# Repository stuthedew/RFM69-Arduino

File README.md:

RFM69-Arduino
=============

Arduino Library for the HopeRF RFM69HW Radio Module

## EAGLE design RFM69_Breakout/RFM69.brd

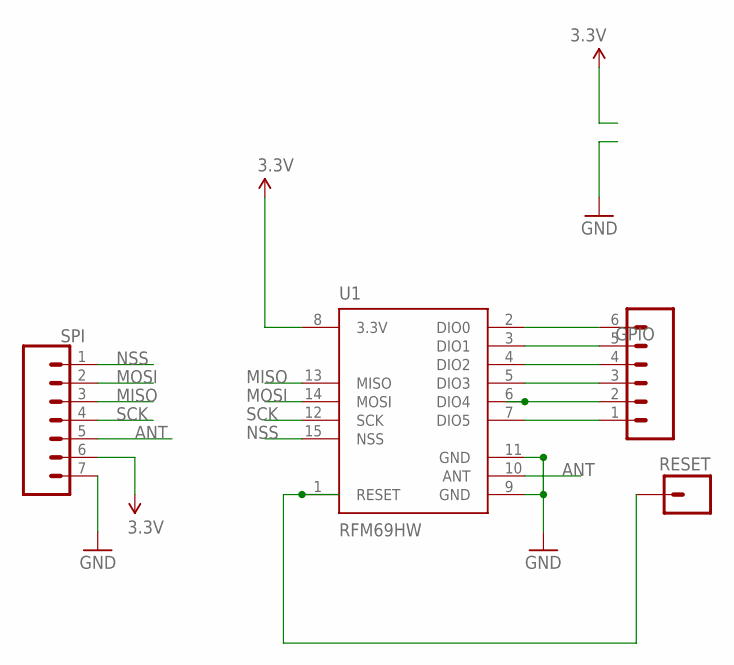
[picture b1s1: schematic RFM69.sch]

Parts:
JP2: RESET; 1X01
JP3: GPIO; 1X06_LOCK
JP4: SPI; 1X07_LOCK
U1: RFM69HW; RFM69W-XXXS2

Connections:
3.3V: JP4.6, U1.8 (3.3V)
ANT: JP4.5, U1.10 (ANT)
DIO0: JP3.6, U1.2 (DIO0)
DIO1: JP3.5, U1.3 (DIO1)
DIO2: JP3.4, U1.4 (DIO2)
DIO3: JP3.3, U1.5 (DIO3)
DIO4: JP3.2, U1.6 (DIO4)
DIO5: JP3.1, U1.7 (DIO5)
GND: JP4.7, U1.9 (GND), U1.11 (GND)
MISO: JP4.3, U1.13 (MISO)
MOSI: JP4.2, U1.14 (MOSI)
NSS: JP4.1, U1.15 (NSS)
RESET: JP2.1, U1.1 (RESET)
SCK: JP4.4, U1.12 (SCK)

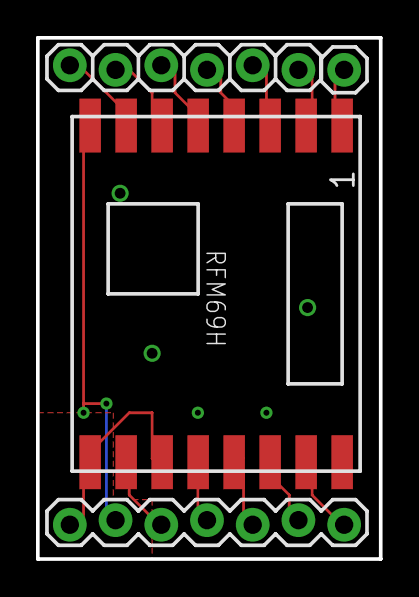
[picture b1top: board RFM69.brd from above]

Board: 2 copper layers, 19.1 x 29.0 mm, 5 parts (1 on the bottom side), 14 nets.

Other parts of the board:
LOGO: SFE_LOGO_NAME_.1

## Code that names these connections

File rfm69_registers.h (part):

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//RSSI value in dBm
#define REG_RSSI_VALUE 0x24

//Mapping of pins DIO0 to DIO3
#define REG_DIO_MAPPING1 0x25
//Mapping of pins DIO4 and DIO5, ClkOut frequency
#define REG_DIO_MAPPING2 0x26

//Status REGister: PLL Lock state, Timeout, RSSI > Threshold
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
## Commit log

2014-07-01 Added config file and register definitions
2014-07-01 Added more register definitions
2014-07-01 Added more register definitions and descriptions
2014-07-02 Added more register definitions.
2014-07-04 Added breakout design files
2014-07-04 Changed file name

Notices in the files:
rfm69_registers.h:
Copyright (c) 2014 Stuart Feichtinger <stuart.feichtinger@gmail.com>
parts and their libraries:
SparkFun-RF: Licensing: Creative Commons ShareAlike 4.0 International - https://creativecommons.org/licenses/by-sa/4.0
